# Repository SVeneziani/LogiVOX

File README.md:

# LogiVOX

**Eyes on the probes. Ears on the measurement.**

[▶ Project video — 1 min 35 s, Full HD](Foto_Video/LogiVOX-presentation.mp4)

LogiVOX is a DIY speaking companion for the **OWON XDM1041**, built by Sergio Veneziani using a Raspberry Pi Zero 2 W, USB communication, a MAX98357A I²S amplifier, a foot pedal and a custom enclosure.

Keep your hands on the probes and let your multimeter speak. Tap a foot pedal for a reading, or enable AUTO to hear stable, meaningful changes. LogiVOX adds a voice to the bench through USB, without opening the multimeter.

[Documentazione italiana](README.it.md) · [Hardware review](docs/HARDWARE-REVIEW.md) · [TALK/AUTO](docs/TALK-AUTO.md)

## Project status

The assembled prototype works and has been tested by its builder. This repository is a **public development snapshot**, not yet a reproducible fabrication release. PCB DRC and schematic/PCB parity checks are clean; print instructions and neutral CAD exports are pending, as are audio redistribution and software licensing.

## Features

- Press the foot pedal or briefly press TALK to hear a reading.
- Hold TALK for two seconds to toggle AUTO, with spoken confirmation.
- AUTO speaks stable, significant changes instead of repeating every few seconds.
- Italian prerecorded number/unit fragments: normal operation does not require a cloud TTS service.
- READY and VOICE indicators.
- Battery-backed orderly shutdown, followed by hardware power disconnection.
- An existing OWON server supplies the USB connection, web dashboard and measurement API.

Only the OWON XDM1041 has been tested with this build. AUTO defaults to off at startup. FORCE OFF cuts power directly; it is not an orderly software shutdown.

## Parts used in the prototype

See the [component links](docs/COMPONENTS.md) for the foot pedal, power module and panel connectors used by the builder.

## Repository layout

- `Software/raspberry/bin/`: voice playback, pedal/TALK/AUTO and UPS services.
- `Software/raspberry/tests/`: hardware-independent logic tests.
- `Software/raspberry/services/`: existing service templates (paths currently reference the prototype user).
- `Software/tools/`: local voice generation helper for macOS.
- `hardware/kicad/`: current schematic/PCB/project snapshot.
- `docs/`: current pinout, operating notes and outstanding hardware review.
- `3D/`: Autodesk Fusion design and Bambu Studio project.
- `enclosure/`: enclosure file inventory and remaining print documentation.
- [Foto_Video/](Foto_Video/): 16 original photographs, the project presentation and a demonstration video.

## Tests

```sh
python3 -m unittest discover -s Software/raspberry/tests -v
```

The optional audio-file presence test is skipped when the voice pack is absent. This does not validate audio playback or the physical UPS.

## Installation status

See [installation notes](docs/INSTALLATION.md). The prototype runs Debian 13 on a Raspberry Pi Zero 2 W. A clean-device installation guide and complete service packaging are still being prepared; do not treat the current files as a one-click installer.

## Credits

- Design, assembly, mechanical enclosure and bench testing: **Sergio Veneziani**.
- Development and troubleshooting assistance: OpenAI ChatGPT/Codex; additional debugging with Cursor.
- USB/web/API backend: [Jason Antman's owon-xdm1041-server](https://github.com/jantman/owon-xdm1041-server), licensed MIT by its author. The backend is a separate dependency and is not vendored here.
- SCPI research credited by that backend: [TheHWcave/OWON-XDM1041](https://github.com/TheHWcave/OWON-XDM1041).
- Initial inspiration: [Arduino-Based Speech Add-on for Modern Multimeters with SCPI Protocol](https://www.pcbway.com/project/shareproject/Arduino_Based_Speech_Add_on_for_Modern_Multimeters_with_SCPI_Protocol_95abefd4.html). The original Arduino sketch is not included in this repository.

## Licensing

Original hardware and enclosure design contributions are offered under **CC BY-NC-SA 4.0**: attribution, noncommercial use and ShareAlike for shared adaptations. Commercial permission and any royalties require a separate written agreement with Sergio Veneziani.

See [licensing scope and exceptions](LICENSE.md). Software, general documentation, photographs/video, third-party materials and voice recordings are not covered by this design-file license. Earlier valid license grants are not revoked.

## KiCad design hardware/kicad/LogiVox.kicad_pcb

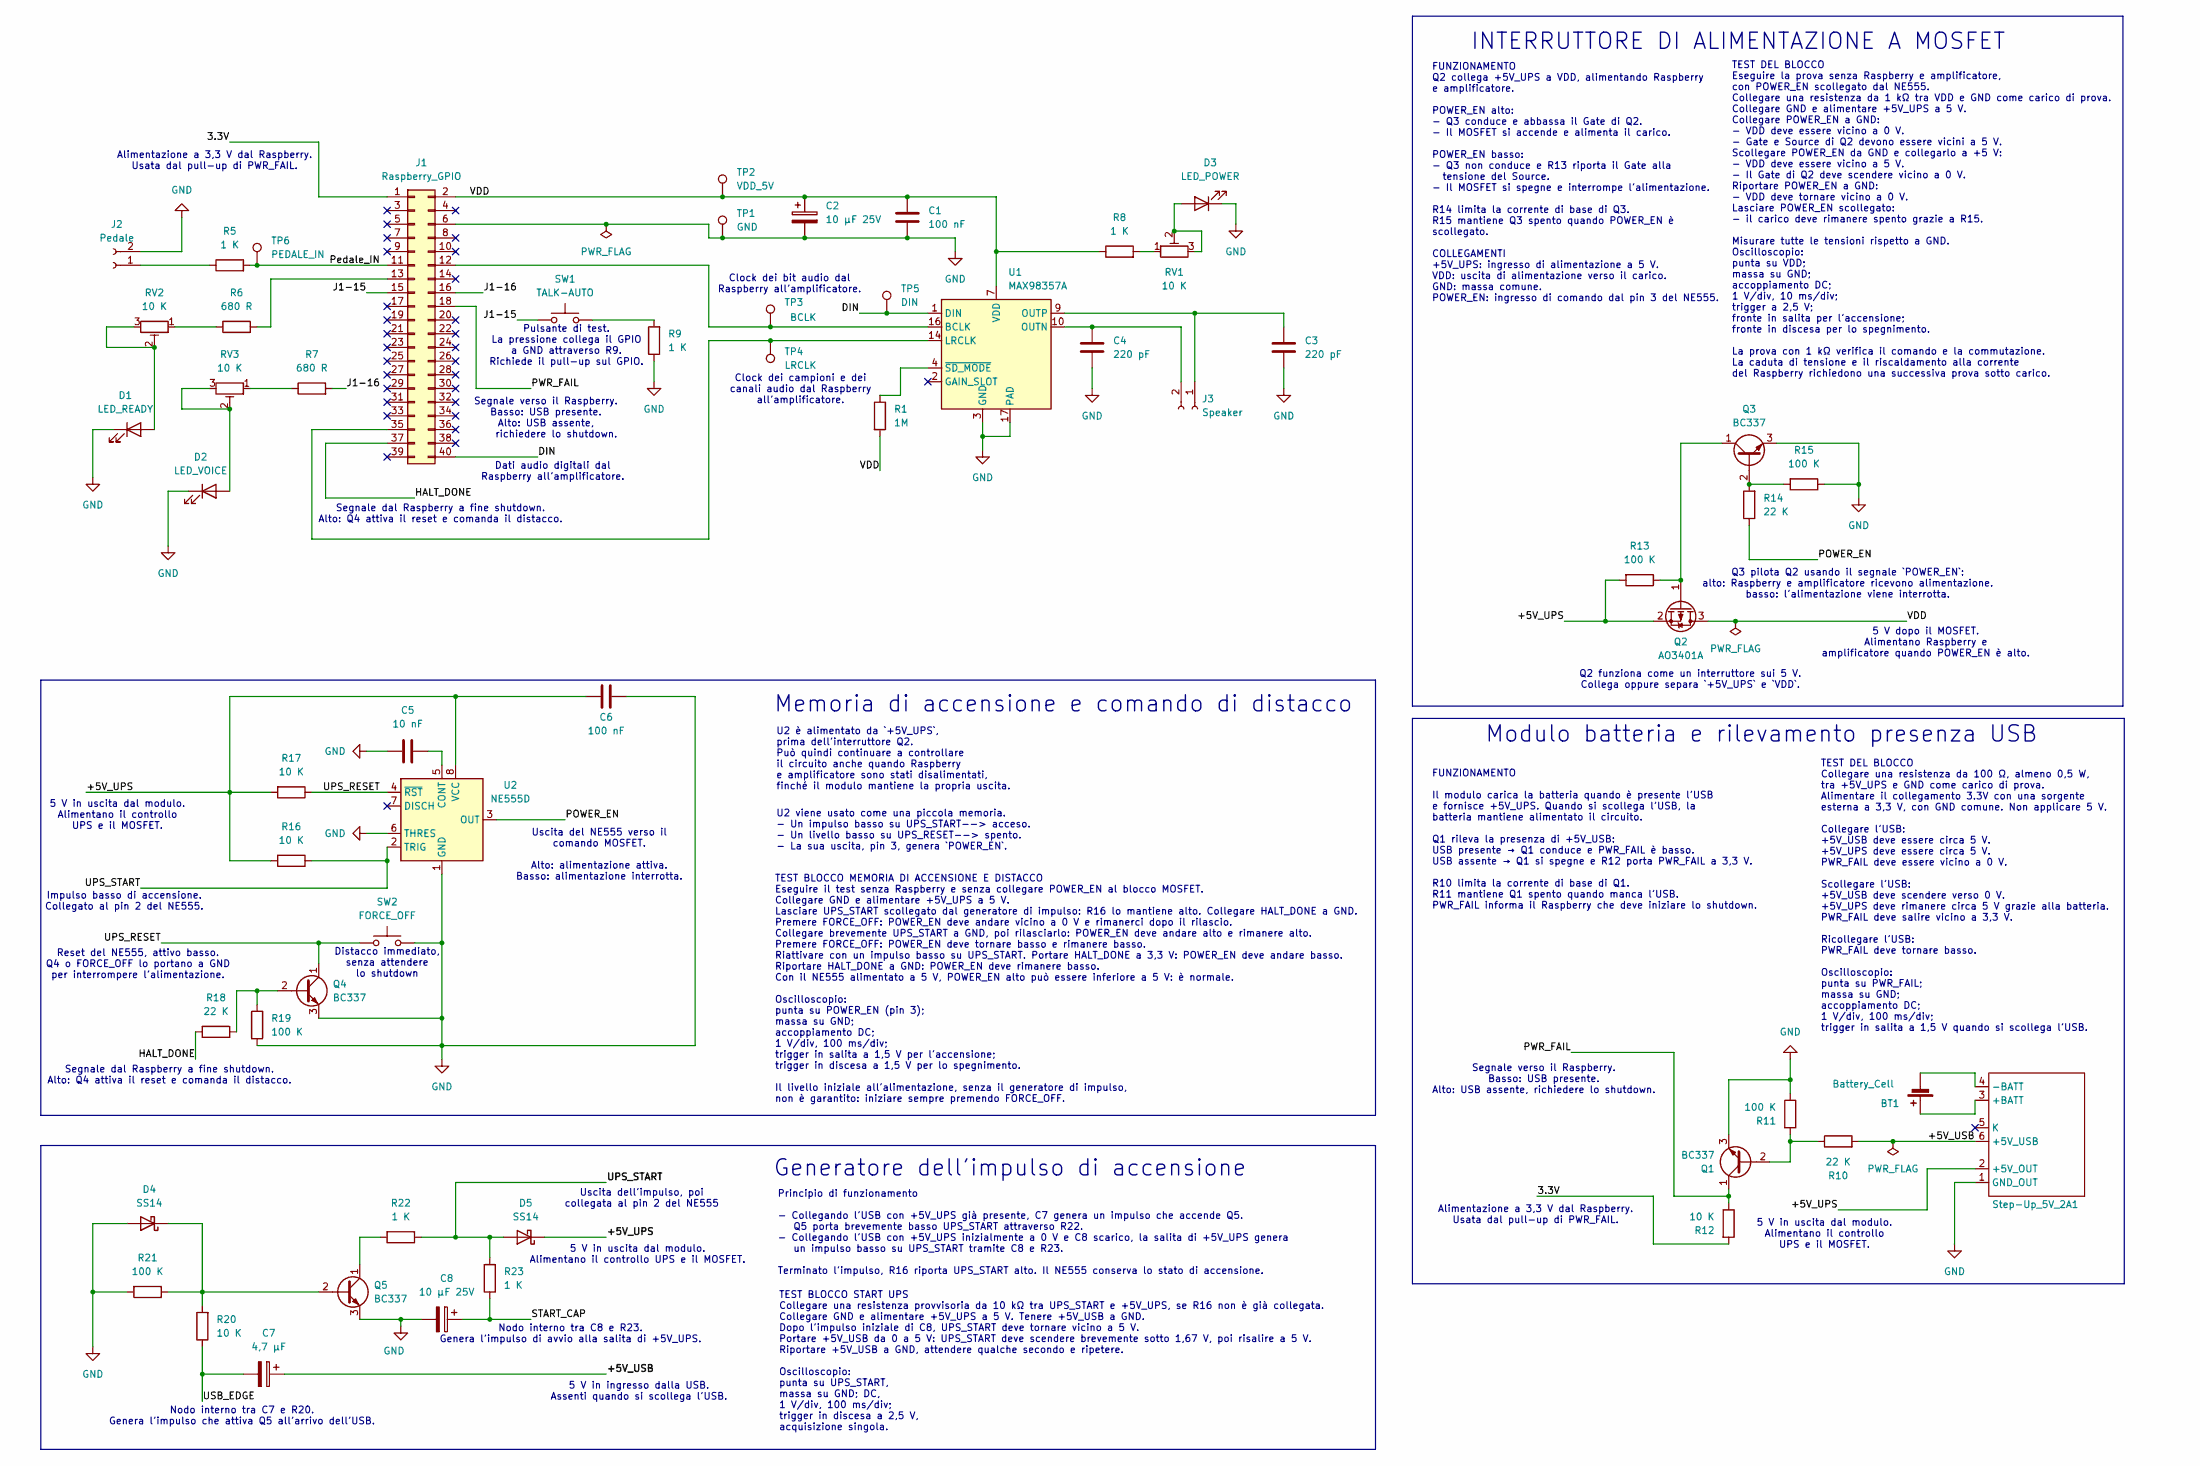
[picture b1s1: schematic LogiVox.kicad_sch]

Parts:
BT1: Battery_Cell
C1, C6: 100 nF; C_0402_1005Metric_Pad0.74x0.62mm_HandSolder
C2, C8: 10 µF 25V; CP_Radial_D4.0mm_P1.50mm
C3, C4: 220 pF; C_0402_1005Metric_Pad0.74x0.62mm_HandSolder
C5: 10 nF; C_0402_1005Metric_Pad0.74x0.62mm_HandSolder
C7: 4,7 µF; CP_Radial_D4.0mm_P1.50mm
D1: LED_READY; LED_D3.0mm
D2: LED_VOICE; LED_D3.0mm
D3: LED_POWER; LED_D3.0mm
D4, D5: SS14; D_SMA
J1: Raspberry_GPIO; PinSocket_2x20_P2.54mm_Vertical
J2: Pedale; PinHeader_1x02_P2.54mm_Vertical
J3: Speaker; PinHeader_1x02_P2.54mm_Vertical
Q1, Q3, Q4, Q5: BC337; TO-92_Inline
Q2: AO3401A; SOT-23
R1: 1M; R_0402_1005Metric_Pad0.72x0.64mm_HandSolder
R5, R8, R9, R22, R23: 1 K; R_0402_1005Metric_Pad0.72x0.64mm_HandSolder
R6, R7: 680 R; R_0402_1005Metric_Pad0.72x0.64mm_HandSolder
R10, R14, R18: 22 K; R_0402_1005Metric_Pad0.72x0.64mm_HandSolder
R11, R13, R15, R19, R21: 100 K; R_0402_1005Metric_Pad0.72x0.64mm_HandSolder
R12, R16, R17, R20: 10 K; R_0402_1005Metric_Pad0.72x0.64mm_HandSolder
RV1, RV2, RV3: 10 K; Potentiometer_Runtron_RM-065_Vertical
SW1: TALK-AUTO; SW_PUSH-12mm
SW2: FORCE_OFF; SW_PUSH-12mm
Step-Up_5V_2A1: Step-Up Regolabile
TP1: GND; TestPoint_Pad_1.5x1.5mm
TP2: VDD_5V; TestPoint_Pad_1.5x1.5mm
TP3: BCLK; TestPoint_Pad_1.5x1.5mm
TP4: LRCLK; TestPoint_Pad_1.5x1.5mm
TP5: DIN; TestPoint_Pad_1.5x1.5mm
TP6: PEDALE_IN; TestPoint_Pad_1.5x1.5mm
U1: MAX98357A; TQFN-16-1EP_3x3mm_P0.5mm_EP1.23x1.23mm_ThermalVias
U2: NE555D; SOIC-8_3.9x4.9mm_P1.27mm

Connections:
/3.3V: J1.1, R12.2
/+5V_UPS: C6.2, D5.1 (K), Q2.2 (S), R13.2, R16.2, R17.2, Step-Up_5V_2A1.2 (+5V_OUT), U2.8 (VCC)
/+5V_USB: C7.1, R10.2, Step-Up_5V_2A1.6 (+5V_USB)
/DIN: J1.40, TP5.1 (1_1), U1.1 (DIN)
/HALT_DONE: J1.37, R18.2
/J1-15: J1.15, SW1.1
/J1-16: J1.16, R7.2
/POWER_EN: R14.1, U2.3 (OUT)
/PWR_FAIL: J1.18, Q1.1 (C), R12.1
/Pedale_IN: J1.11, R5.2, TP6.1 (1_1)
/START_CAP: C8.1, R23.1
/UPS_RESET: Q4.1 (C), R17.1, SW2.1, U2.4 (~RST)
/UPS_START: D5.2 (A), R16.1, R22.1, R23.2, U2.2 (TRIG)
/USB_EDGE: C7.2, R20.1
/VDD: C1.1, C2.1, J1.2, Q2.3 (D), R1.2, R8.1, TP2.1 (1_1), U1.7 (VDD), U1.8 (VDD)
GND: C1.2, C2.2, C3.2, C4.2, C5.2, C6.1, C8.2, D1.1 (K), D2.1 (K), D3.1 (K), D4.2 (A), J1.6, J2.2, Q1.3 (E), Q3.3 (E), Q4.3 (E), Q5.3 (E), R9.1, R11.1, R15.1, R19.1, R21.2, SW2.2, Step-Up_5V_2A1.1 (GND_OUT), TP1.1 (1_1), U1.3 (GND), U1.11 (GND), U1.15 (GND), U1.17 (PAD), U2.1 (GND), U2.6 (THRES)
unnamed: D1.2 (A), RV2.2, RV2.3
unnamed: D2.2 (A), RV3.2, RV3.3
unnamed: D3.2 (A), RV1.2, RV1.3
unnamed: D4.1 (K), Q5.2 (B), R20.2, R21.1
unnamed: J1.12, TP3.1 (1_1), U1.16 (BCLK)
unnamed: J1.13, R6.2
unnamed: J1.35, TP4.1 (1_1), U1.14 (LRCLK)
unnamed: J2.1, R5.1
unnamed: C3.1, J3.1, U1.9 (OUTP)
unnamed: C4.1, J3.2, U1.10 (OUTN)
unnamed: Q1.2 (B), R10.1, R11.2
unnamed: Q2.1 (G), Q3.1 (C), R13.1
unnamed: Q3.2 (B), R14.2, R15.2
unnamed: Q4.2 (B), R18.1, R19.2
unnamed: Q5.1 (C), R22.2
unnamed: R6.1, RV2.1
unnamed: R7.1, RV3.1
unnamed: R8.2, RV1.1
unnamed: R9.2, SW1.2
unnamed: BT1.1 (+), Step-Up_5V_2A1.3 (+BATT)
unnamed: BT1.2 (-), Step-Up_5V_2A1.4 (-BATT)
unnamed: R1.1, U1.4 (~SD_MODE)
unnamed: C5.1, U2.5 (CONT)

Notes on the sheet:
Reset del NE555, attivo basso. Q4 o FORCE_OFF lo portano a GND per interrompere l’alimentazione.
Nodo interno tra C7 e R20. Genera l’impulso che attiva Q5 all’arrivo dell’USB.
Q2 funziona come un interruttore sui 5 V. Collega oppure separa `+5V_UPS` e `VDD`.
Impulso basso di accensione. Collegato al pin 2 del NE555.
Alimentazione a 3,3 V dal Raspberry. Usata dal pull-up di PWR_FAIL.
Uscita dell'impulso, poi collegata al pin 2 del NE555
5 V in uscita dal modulo. Alimentano il controllo UPS e il MOSFET.
INTERRUTTORE DI ALIMENTAZIONE A MOSFET
Distacco immediato, senza attendere lo shutdown
Uscita del NE555 verso il comando MOSFET. Alto: alimentazione attiva. Basso: alimentazione interrotta.
Generatore dell'impulso di accensione
Segnale dal Raspberry a fine shutdown. Alto: Q4 attiva il reset e comanda il distacco.
Modulo batteria e rilevamento presenza USB
TEST BLOCCO MEMORIA DI ACCENSIONE E DISTACCO Eseguire il test senza Raspberry e senza collegare POWER_EN al blocco MOSFET. Collegare GND e alimentare +5V_UPS a 5 V. Lasciare UPS_START scollegato dal generatore di impulso: R16 lo mantiene alto. Collegare HALT_DONE a GND. Premere FORCE_OFF: POWER_EN 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
5 V in uscita dal modulo. Alimentano il controllo UPS e il MOSFET.
Memoria di accensione e comando di distacco
Segnale verso il Raspberry. Basso: USB presente. Alto: USB assente, richiedere lo shutdown.
TEST DEL BLOCCO Collegare una resistenza da 100 Ω, almeno 0,5 W, tra +5V_UPS e GND come carico di prova. Alimentare il collegamento 3.3V con una sorgente esterna a 3,3 V, con GND comune. Non applicare 5 V. Collegare l’USB: +5V_USB deve essere circa 5 V. +5V_UPS deve essere circa 5 V. PWR_FAIL deve 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
FUNZIONAMENTO Il modulo carica la batteria quando è presente l’USB e fornisce +5V_UPS. Quando si scollega l’USB, la batteria mantiene alimentato il circuito. Q1 rileva la presenza di +5V_USB: USB presente → Q1 conduce e PWR_FAIL è basso. USB assente → Q1 si spegne e R12 porta PWR_FAIL a 3,3 V. R10 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
TEST BLOCCO START UPS Collegare una resistenza provvisoria da 10 kΩ tra UPS_START e +5V_UPS, se R16 non è già collegata. Collegare GND e alimentare +5V_UPS a 5 V. Tenere +5V_USB a GND. Dopo l'impulso iniziale di C8, UPS_START deve tornare vicino a 5 V. Portare +5V_USB da 0 a 5 V: UPS_START deve sce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
Clock dei campioni e dei canali audio dal Raspberry all’amplificatore.
Dati audio digitali dal Raspberry all’amplificatore.
Nodo interno tra C8 e R23. Genera l’impulso di avvio alla salita di +5V_UPS.
Pulsante di test. La pressione collega il GPIO a GND attraverso R9. Richiede il pull-up sul GPIO.
Principio di funzionamento - Collegando l'USB con +5V_UPS già presente, C7 genera un impulso che accende Q5. Q5 porta brevemente basso UPS_START attraverso R22. - Collegando l'USB con +5V_UPS inizialmente a 0 V e C8 scarico, la salita di +5V_UPS genera un impulso basso su UPS_START tramite C8 e R23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
TEST DEL BLOCCO Eseguire la prova senza Raspberry e amplificatore, con POWER_EN scollegato dal NE555. Collegare una resistenza da 1 kΩ tra VDD e GND come carico di prova. Collegare GND e alimentare +5V_UPS a 5 V. Collegare POWER_EN a GND: - VDD deve essere vicino a 0 V. - Gate e Source di Q2 devono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
Q3 pilota Q2 usando il segnale `POWER_EN`: alto: Raspberry e amplificatore ricevono alimentazione. basso: l'alimentazione viene interrotta.
U2 viene usato come una piccola memoria. - Un impulso basso su UPS_START--> acceso. - Un livello basso su UPS_RESET--> spento. - La sua uscita, pin 3, genera `POWER_EN`.
Clock dei bit audio dal Raspberry all’amplificatore.
5 V in ingresso dalla USB. Assenti quando si scollega l'USB.
Segnale verso il Raspberry. Basso: USB presente. Alto: USB assente, richiedere lo shutdown.
FUNZIONAMENTO Q2 collega +5V_UPS a VDD, alimentando Raspberry e amplificatore. POWER_EN alto: - Q3 conduce e abbassa il Gate di Q2. - Il MOSFET si accende e alimenta il carico. POWER_EN basso: - Q3 non conduce e R13 riporta il Gate alla tensione del Source. - Il MOSFET si spegne e interrompe l'alim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
5 V dopo il MOSFET. Alimentano Raspberry e amplificatore quando POWER_EN è alto.
U2 è alimentato da `+5V_UPS`, prima dell'interruttore Q2. Può quindi continuare a controllare il circuito anche quando Raspberry e amplificatore sono stati disalimentati, finché il modulo mantiene la propria uscita.

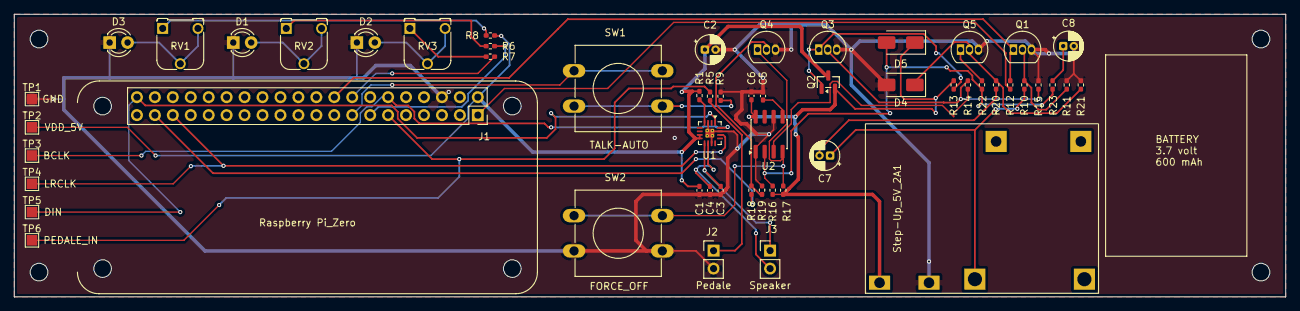
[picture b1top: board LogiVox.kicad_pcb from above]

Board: 2 copper layers, 180.0 x 40.0 mm, 63 parts (0 on the bottom side), 37 nets.

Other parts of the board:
HE1, HE2, HE3, HE4: MountingHole_2.5mm
HI1, HI2, HI3, HI4: MountingHole_2.5mm
